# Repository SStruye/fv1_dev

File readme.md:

# FV1 dev board
the FV1 is a widely used reverb/effect I2C that is programmable.
I build a dev board around it for use as a guitar pedal design platform. <br>

the devboard provides:
-  an onboard usb programmer
-  buffered in and output
-  3 positional dip switch for the FV1,
-  3 variable resistor for the FV1 
-  1 variable resistor for volume 
-  1 variable resistor for mixing the clean and effects signal.

The 3 dip switch can be used to select presets or for use with custom software. The 3 variable resistors are there to adjust paramaters such as time, rise, rate, depth etc. <br>
a 4 layer pcb design was made for better signal integrity.
Some small mistakes are still in the design but it works. (e.g. wrong 3.3V regulator footprint)
Further improvements won't be added for the foreseeable future as intrests shifted.

## PCB design

## result

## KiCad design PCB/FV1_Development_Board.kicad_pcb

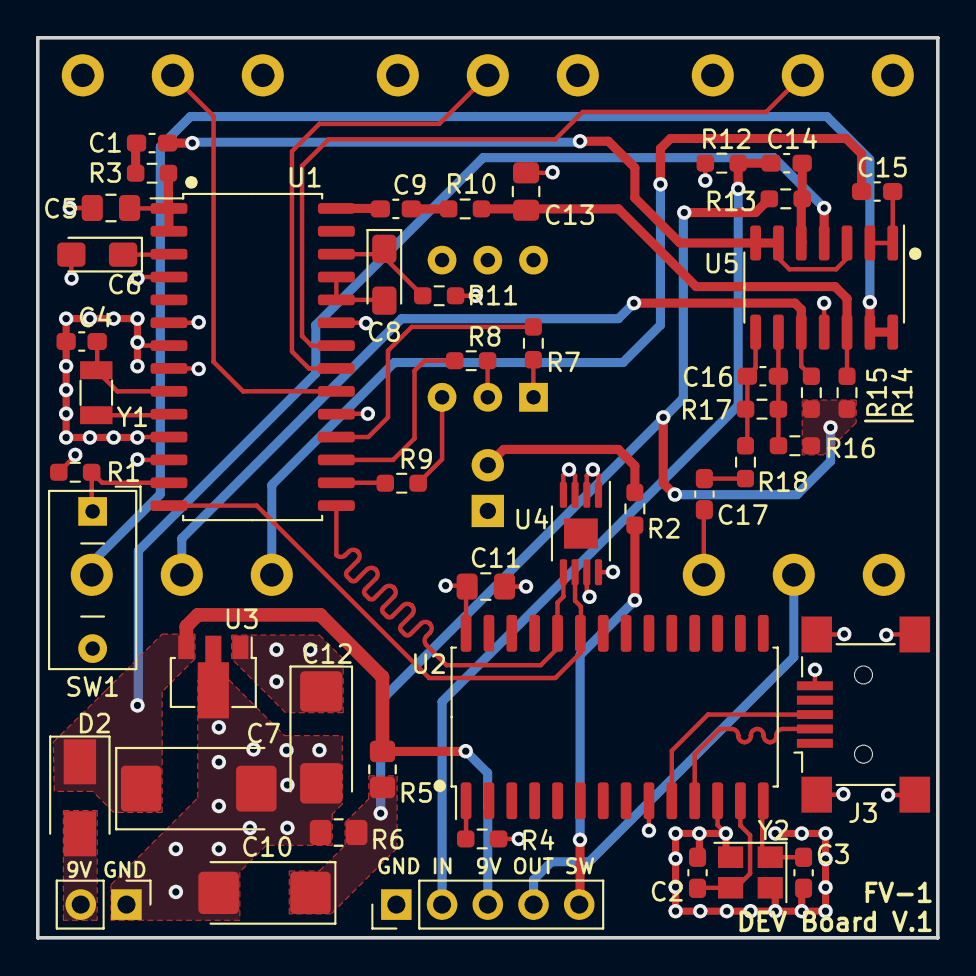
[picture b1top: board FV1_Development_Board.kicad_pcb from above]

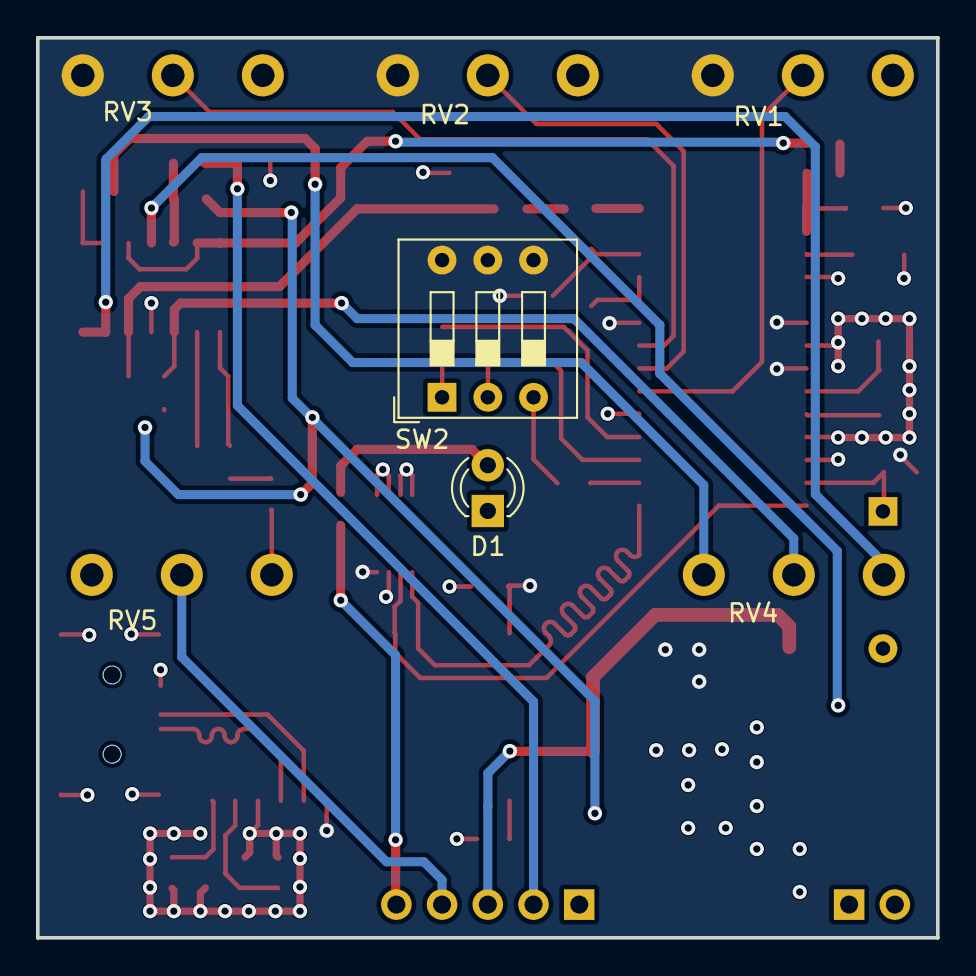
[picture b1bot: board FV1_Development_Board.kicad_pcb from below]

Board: 4 copper layers, 50.0 x 50.0 mm, 54 parts (7 on the bottom side), 46 nets.

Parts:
9V GND: 9V DC; PinHeader_1x02_P2.54mm_Vertical
C1, C9, C15, C17: 1u; C_0603_1608Metric_Pad1.08x0.95mm_HandSolder
C2, C3: 18p; C_0603_1608Metric_Pad1.08x0.95mm_HandSolder
C4: 12p; C_0603_1608Metric_Pad1.08x0.95mm_HandSolder
C5: 1n; C_0805_2012Metric_Pad1.18x1.45mm_HandSolder
C6, C8: 1u; CP_EIA-3216-10_Kemet-I_Pad1.58x1.35mm_HandSolder
C7: 100u; CP_EIA-7343-20_Kemet-V_Pad2.25x2.55mm_HandSolder
C10, C12: 47u; CP_EIA-6032-28_Kemet-C_Pad2.25x2.35mm_HandSolder
C11: 100n; C_0805_2012Metric_Pad1.18x1.45mm_HandSolder
C13: 2n2; C_0805_2012Metric_Pad1.18x1.45mm_HandSolder
C14: 100n; C_0603_1608Metric_Pad1.08x0.95mm_HandSolder
C16: 120p; C_0603_1608Metric_Pad1.08x0.95mm_HandSolder
D1: LED; LED_D3.0mm
D2: S1D; D_SMA
GND IN  9V OUT SW: Conn_01x05_Female; PinHeader_1x05_P2.54mm_Vertical
J3: USB_B_Mini; USB_Mini-B_Lumberg_2486_01_Horizontal
R1, R7, R8, R9: 20k; R_0603_1608Metric_Pad0.98x0.95mm_HandSolder
R2: 4k7; R_0603_1608Metric_Pad0.98x0.95mm_HandSolder
R3, R10: 1k; R_0603_1608Metric_Pad0.98x0.95mm_HandSolder
R4: 2k2; R_0603_1608Metric_Pad0.98x0.95mm_HandSolder
R5, R6: 10k; R_0805_2012Metric_Pad1.20x1.40mm_HandSolder
R11, R18: 100R; R_0603_1608Metric_Pad0.98x0.95mm_HandSolder
R12: 1M; R_0603_1608Metric_Pad0.98x0.95mm_HandSolder
R13, R14, R15: 100k; R_0603_1608Metric_Pad0.98x0.95mm_HandSolder
R16: 10k; R_0603_1608Metric_Pad0.98x0.95mm_HandSolder
R17: 200k; R_0603_1608Metric_Pad0.98x0.95mm_HandSolder
RV1: POT0; Potentiometer_Omeg_PC16BU_Vertical
RV2: POT1; Potentiometer_Omeg_PC16BU_Vertical
RV3: POT2; Potentiometer_Omeg_PC16BU_Vertical
RV4: MIX; Potentiometer_Omeg_PC16BU_Vertical
RV5: VOL; Potentiometer_Omeg_PC16BU_Vertical
SW1: DIP_X1; SW_DIP_SPSTx01_Slide_9.78x4.72mm_W7.62mm_P2.54mm
SW2: DIP_X3; SW_DIP_SPSTx03_Slide_9.78x9.8mm_W7.62mm_P2.54mm
U1: FV-1; FV1
U2: CH341A
U3: AZ1117CR_SOT89; SOT-89-3
U4: 24LC32; MSOP-8-1EP_3x3mm_P0.65mm_EP1.68x1.88mm
U5: TL074; SOIC-14_3.9x8.7mm_P1.27mm
Y1: JTX310; Crystal_SMD_3215-2Pin_3.2x1.5mm
Y2: 12MHz; Crystal_SMD_Abracon_ABM8G-4Pin_3.2x2.5mm

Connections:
/3V3: C11.2, C12.1, R1.1, R11.2, RV1.3, RV2.3, RV3.3, SW2.4, SW2.5, SW2.6, U1.6 (AVDD), U1.8 (DVDD), U1.23 (DVDD), U2.9 (V3), U2.28 (VCC), U3.1 (OUT), U4.8 (VCC)
/9V: C7.1, D2.1 (K), GND IN 9V OUT SW.3, R5.2, U3.3 (IN), U5.4 (V+)
/BUF_IN: C1.1, U5.3 (+), U5.6 (-), U5.7
/BUF_OUT: RV4.1, U5.13 (-), U5.14
/D+: J3.3 (D+), U2.10 (UD+)
/D-: J3.2 (D-), U2.11 (UD-)
/Eff in: C14.1, GND IN 9V OUT SW.2, R12.2
/Eff out: GND IN 9V OUT SW.4, RV5.2
/OUT: C13.1, R10.2, R14.2, U5.12 (+)
/POT0: RV1.2, U1.20 (POT0)
/POT1: RV2.2, U1.21 (POT1)
/POT2: RV3.2, U1.22 (POT2)
/SCL: U1.14 (SCK), U2.23 (SDA), U4.6 (SCL)
/SDA: U1.15 (SDA), U2.24 (SCL), U4.5 (SDA)
/VREF: C10.1, R5.1, R6.2, R13.1, R14.1, R15.2, R16.1
GND: 9V GND.1, C2.2, C3.2, C4.2, C5.1, C6.2, C7.2, C10.2, C11.1, C12.2, C13.2, D1.1 (K), GND IN 9V OUT SW.1, J3.5 (GND), J3.6 (Shield), R4.1, R6.1, R12.1, RV1.1, RV2.1, RV3.1, RV5.3, SW1.2, U1.4 (GND), U1.7 (GND), U1.11 (GND), U1.12 (T1), U1.19 (GND), U2.12 (GND), U3.2 (GND), U4.1 (A0), U4.2 (A1), U4.3 (A2), U4.4 (GND), U4.7 (WP), U5.11 (V-), Y2.2, Y2.4
unnamed: C1.2, R3.1
unnamed: C2.1, U2.13 (XI), Y2.3
unnamed: C3.1, U2.14 (XO), Y2.1
unnamed: C4.1, U1.9 (X2), Y1.1
unnamed: C5.2, R3.2, U1.1 (VIN), U1.2 (RIN)
unnamed: C6.1, U1.3 (MID)
unnamed: C8.1, R11.1, U1.26 (REFP)
unnamed: C8.2, U1.24 (GND), U1.25 (REFN)
unnamed: C9.1, U1.28 (LOUT)
unnamed: C9.2, R10.1
unnamed: C14.2, R13.2, U5.5 (+)
unnamed: C15.1, U5.1, U5.2 (-)
unnamed: C15.2, RV4.3
unnamed: C16.1, R16.2, R17.1, U5.9 (-)
unnamed: C16.2, R17.2, R18.1, U5.8
unnamed: C17.1, R18.2
unnamed: C17.2, RV5.1
unnamed: D1.2 (A), R2.1
unnamed: 9V GND.2, D2.2 (A)
unnamed: GND IN 9V OUT SW.5, R2.2
unnamed: R1.2, SW1.1, U1.13 (T0)
unnamed: R4.2, U2.1 (ACT#)
unnamed: R7.1, SW2.1
unnamed: R7.2, U1.18 (S2)
unnamed: R8.1, SW2.2
unnamed: R8.2, U1.17 (S1)
unnamed: R9.1, SW2.3
unnamed: R9.2, U1.16 (S0)
unnamed: R15.1, RV4.2, U5.10 (+)
unnamed: U1.10 (X1), Y1.2

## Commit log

2023-06-04 Create x
